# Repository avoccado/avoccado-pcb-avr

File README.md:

Avoccado° PCB layouts and schematics
================

**Most recent version: Avoccado° Felina**

This repository contains the source files of the PCBs for Avoccado° controllers equipped with AVR micro controllers.

There are different PCBs, some with more than one revision. Check the commit log for the most recent development version.

 - Alpha 1 (A1): 8/10 mil width/spacing, 2 sided, components on one side, full size rectangular board a la Arduino Nano / Pro Mini with female micro USB 2.0 and LiPo charger
 - Kane: 8/8 mil, small square board without LiPo charger, components on both sides, good as a tiny RX (receiver) node.
 - Yolandi: 8/8 mil, never tested
 - Nora 1: square board, about one square inch, IRQ from NRF24 routed to MCU
 - Nora 2: same as Nora 1 with IRQ from NRF24 and MPU6050 routed to MCU
 - Faye: updated Nora 2 with voltage divider to sense battery voltage and derive SOC (state of charge), added optional micro USB SMD socket on bottom layer, optionally less part diversity count as R_charge-program can be set with two serialised 1K 0402 resistors. Faye has got an equal 100 mil grid for every pin header and test point.
 - Felina: Features like Faye, without 0402 R_charge-program, non-square footprint, with MPU6050 QFN on board (optional), USB SMD on bottom layer
 - Gin: Board layout smaller than one NRF24L01 PCB module, features AtMega328 QFN + MPU6050 QFN. Not possible to hand solder, very small overall footprint. USB connector only passive (for charging)

Alpha 1 (A1):
----------------

USB bootloader option to update the firmware if the 68R resistors are populated. The USB data lines connect to D2 and D7.
There is a 2K pullup to 3.3V at the D- USB data line, no zener diodes to limit the voltage at the data lines because the MCU runs at USB compliant 3.3V VCC, see vUSB recommendations here: http://vusb.wikidot.com/hardware

Kane
----------------

Smallest version when MPU6050 board not used. Hard to populate due to parts on both sides. Good for tiny receiver nodes, can be hidden in the E27 socket of a light bulb, wall socket..

Nora
----------------

Notes and ideas: No cinsistent 100 mil grid with all headers at the moment
Plated half holes are nice for SMD piggybacking the hole board. Mind the test points and exposed pads on the bottom.

Faye
----------------

Consistent 100 mil grid for all pin headers, additional test points (all conforming the 100 mil grid).
Tighter spacing with 0402 parts now close to the MCU and border of the board.
Battery voltage fed into ADC portpin through high impedance voltage divider to estimate SOC with the MCU.
Optional micro USB socket on the bottom. Data lines not used as of now due to routing constraints, only used for power and charging LiPo batteries.

Felina
----------------

InvenSense MPU6000 / MPU6050 QFN package on board instead of peripheral daughter board. Header for peripheral board still available. Slim rectangular design, slightly longer due to additional parts for onboard MPU, thus only 10 PCBs per panel instead of the usual 16.
Battery voltage fed into ADC portpin through high impedance voltage divider to estimate SOC with the MCU.
Optional: Micro USB female on bottom side for charging
Optional: V-USB components with 2K pullup on D- to enable USB firmware usage. (needs airwire for one data line) 
Attention: V-USB uses same D2 IRQ line as MPU6050.
Consistent 100 mil grid for all pin headers, additional test points, SMD pad for vibration motor output.

Gin
----------------

InvenSense MPU6050 QFN package, Atmel AtMega328p QFN package, very small overall footprint, smaller than a NRF24 module. No seperate ICSP header, flashing only via test points and the NRF24 connector. No DTR reset latch with capacitor.
Consistent 100 mil grid for all headers and test points. 

Panels 
----------------

Boards are either panelized to 50 x 50 mm² or 100 x 100 mm² because my test jig can hold those two sizes. PCBs are usually placed on a 25 mm grid - that is slightly below one inch (25.4 mm).

Test jigs
----------------
Nora 2 test jig is compatible with Nora 1 and Nora 2
See separate repository for test jig assemblies

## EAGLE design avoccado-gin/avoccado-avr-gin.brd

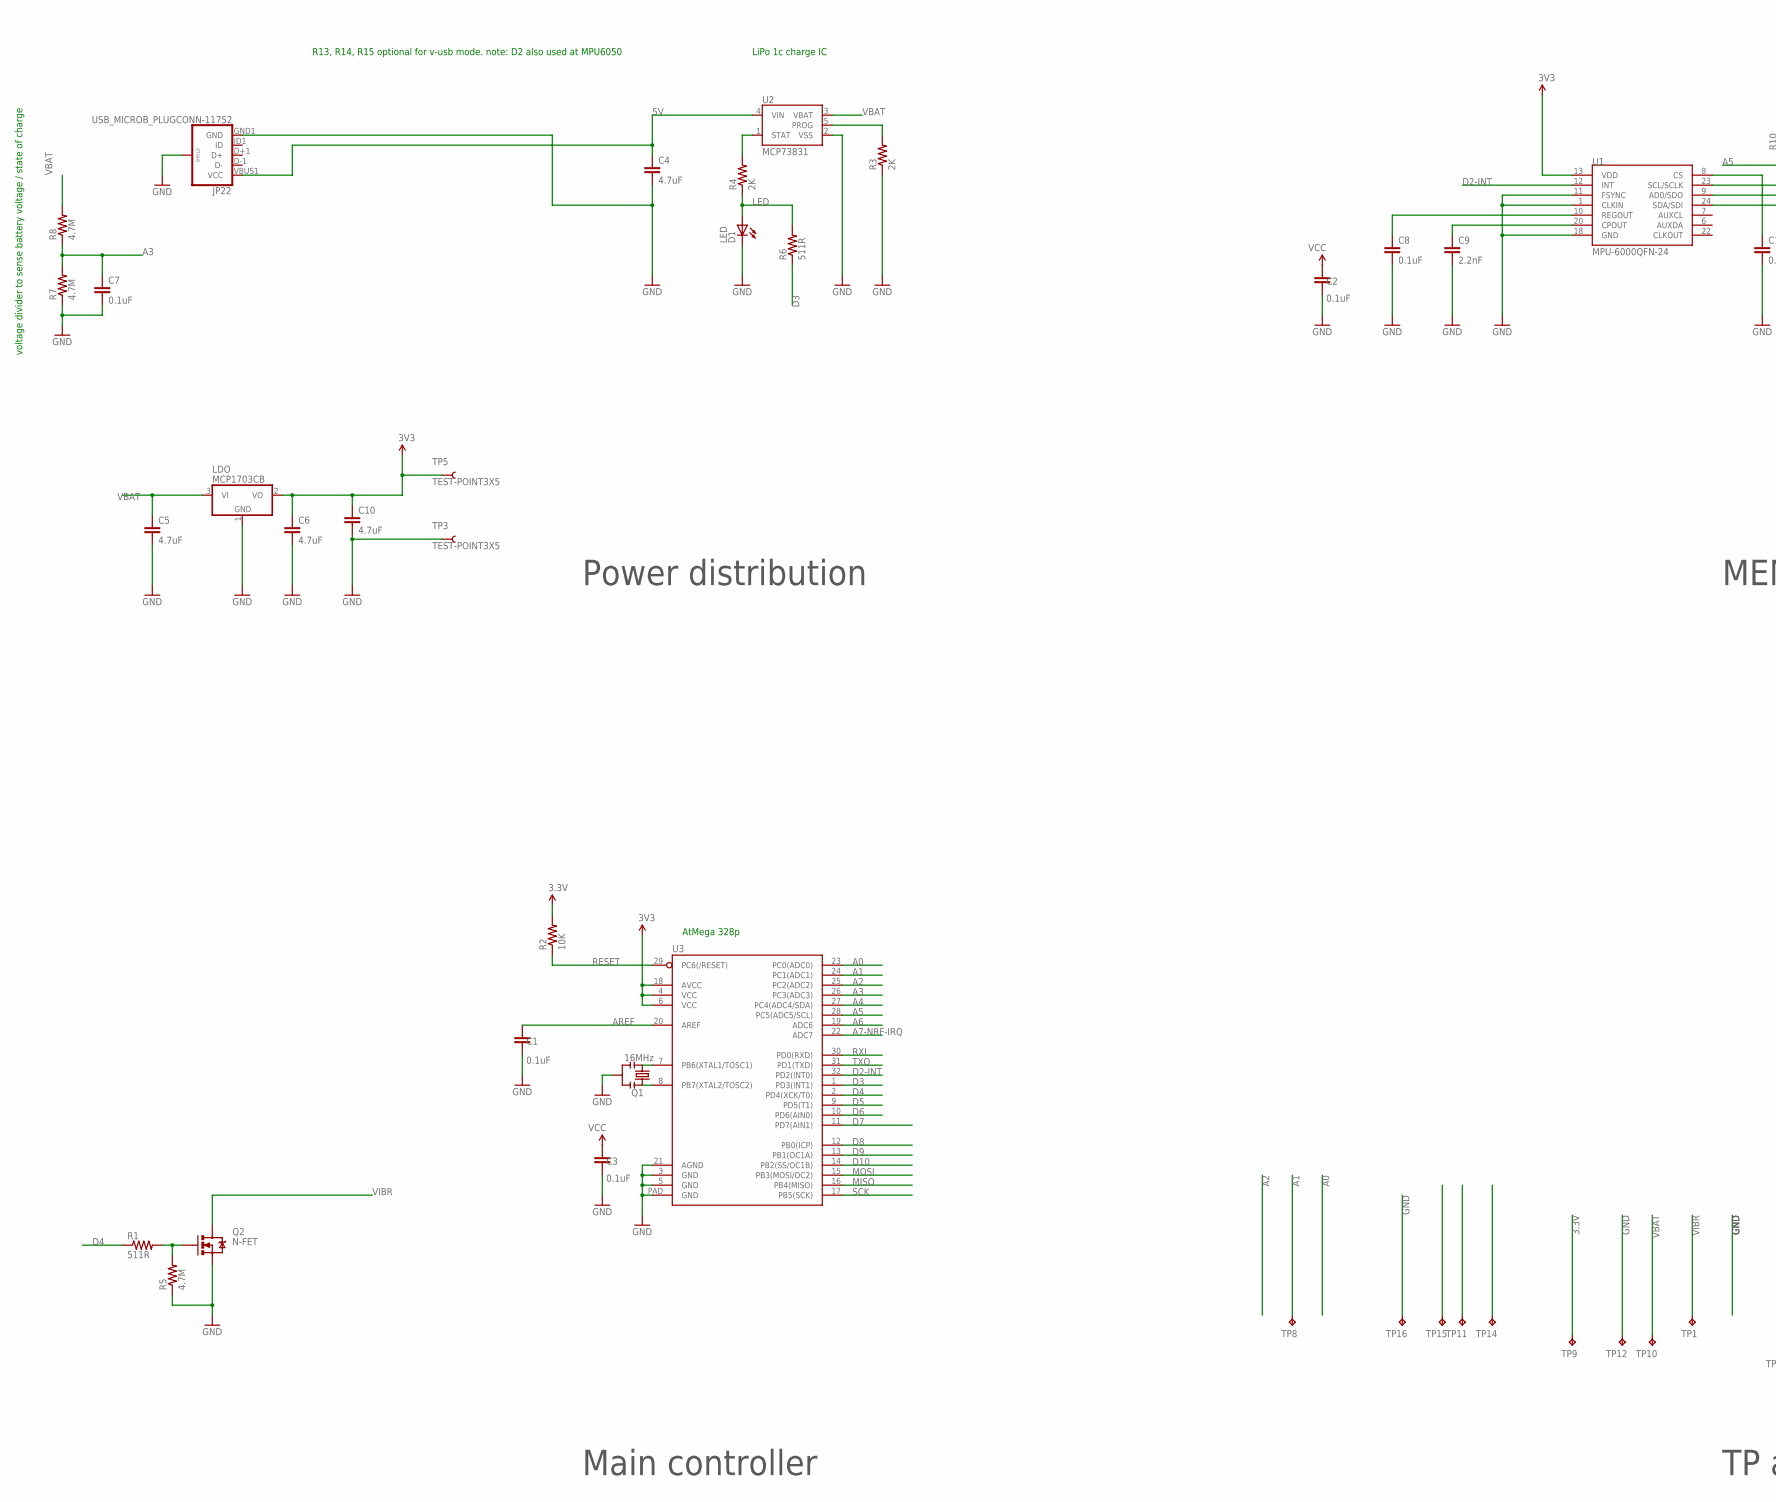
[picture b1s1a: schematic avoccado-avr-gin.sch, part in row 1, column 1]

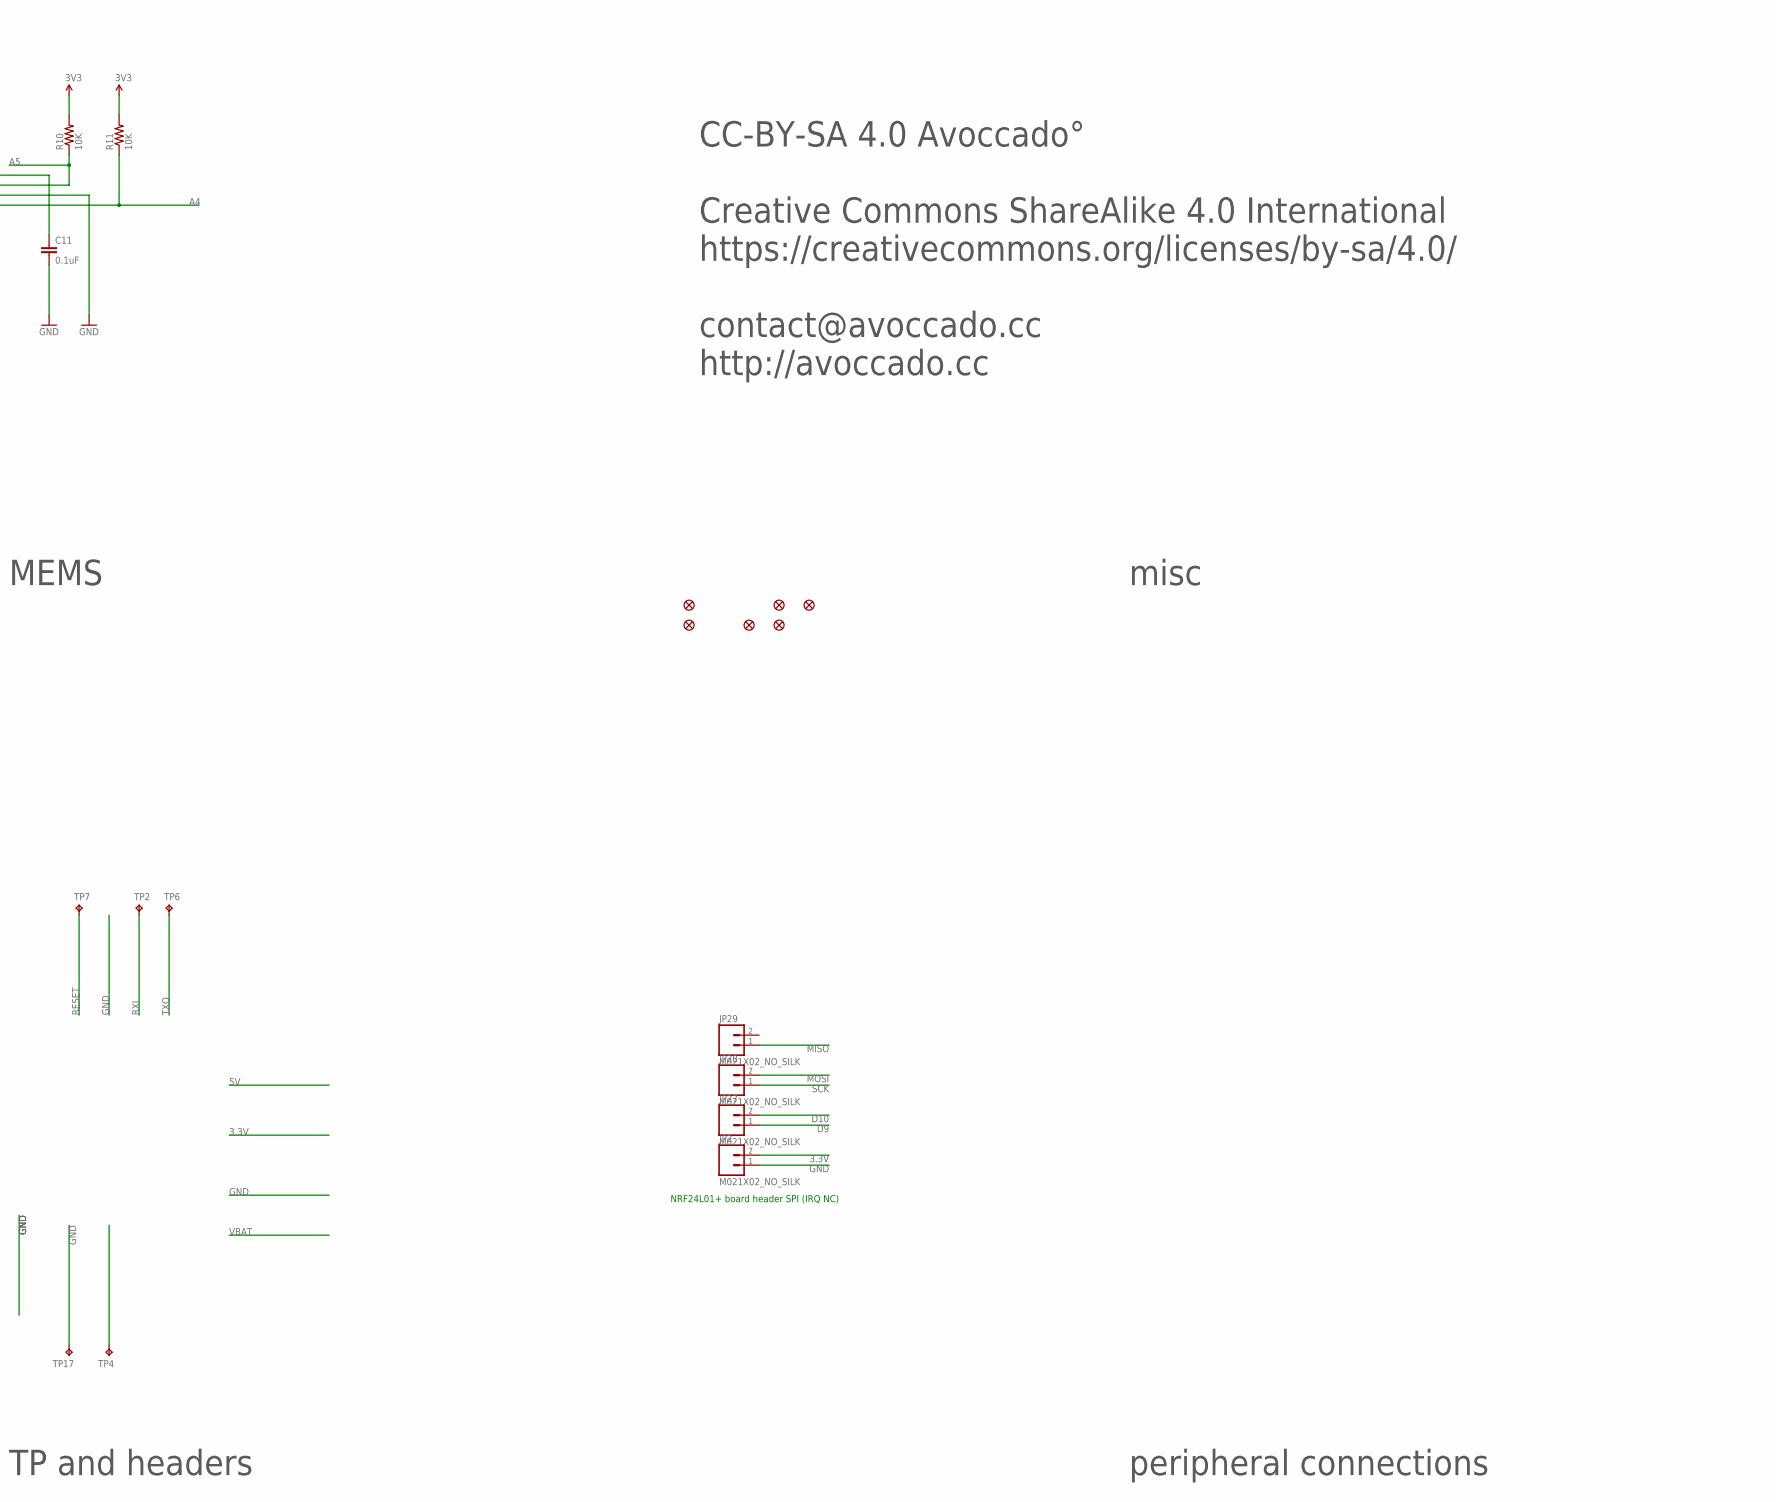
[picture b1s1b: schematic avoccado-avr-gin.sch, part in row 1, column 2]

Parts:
C1, C2, C3, C7, C8, C11: 0.1uF; C0402K
C4, C5, C6: 4.7uF; 0603-CAP
C9: 2.2nF; C0402K
C10: 4.7uF; C0603
D1: LED; LED-0603
FID2, FID4, FID5, FID6, FID8, FID9: FIDUCIALUFIDUCIAL; MICRO-FIDUCIAL
JP2, JP27, JP28, JP29: M021X02_NO_SILK; 1X02_NO_SILK
JP22: USB_MICROB_PLUGCONN-11752; USB-B-MICRO-SMD_V03
LDO: MCP1703CB; SOT23
Q1: 16MHz; RESONATOR-SMD
Q2: N-FET; SOT23-3
R1, R6: 511R; 0603-RES
R2, R10, R11: 10K; 0603-RES
R3, R4: 2K; 0603-RES
R5, R7, R8: 4.7M; 0603-RES
TP1, TP2, TP4, TP6, TP7, TP8, TP9, TP10, TP11, TP12, TP14, TP15, TP16, TP17: TPTP20R; TP20R
TP3, TP5: TEST-POINT3X5; PAD.03X.05
U1: MPU-6000QFN-24; QFN-24-TESTING
U2: MCP73831; SOT23-5
U3: ATMEGA328P_MLFMLF32; MLF32-PAD

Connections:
3.3V: C2.2, C3.2, C6.1, C10.1, JP2.2, LDO.2 (VO), R2.2, R10.2, R11.2, TP5.P$1, TP9.TP, U1.13 (VDD), U3.4 (VCC), U3.6 (VCC), U3.18 (AVCC)
5V: C4.1, JP22.VBUS1 (VCC), U2.4 (VIN)
A0: U3.23 (PC0(ADC0))
A1: TP8.TP, U3.24 (PC1(ADC1))
A2: U3.25 (PC2(ADC2))
A3: C7.1, R7.2, R8.1, U3.26 (PC3(ADC3))
A4: R11.1, U1.24 (SDA/SDI), U3.27 (PC4(ADC4/SDA))
A5: R10.1, U1.23 (SCL/SCLK), U3.28 (PC5(ADC5/SCL))
A6: U3.19 (ADC6)
A7-NRF-IRQ: U3.22 (ADC7)
AREF: C1.2, U3.20 (AREF)
CHG-PROG: R3.2, U2.5 (PROG)
D2-INT: U1.12 (INT), U3.32 (PD2(INT0))
D3: R6.1, U3.1 (PD3(INT1))
D4: R1.1, U3.2 (PD4(XCK/T0))
D5: TP15.TP, U3.9 (PD5(T1))
D6: U3.10 (PD6(AIN0))
D7: TP14.TP, U3.11 (PD7(AIN1))
D8: TP11.TP, U3.12 (PB0(ICP))
D9: JP27.1, U3.13 (PB1(OC1A))
D10: JP27.2, U3.14 (PB2(SS/OC1B))
GND: C1.1, C2.1, C3.1, C4.2, C5.2, C6.2, C7.2, C8.2, C9.2, C10.2, C11.2, D1.C, JP2.1, JP22.GND1 (GND), JP22.SHIELD1 (SHIELD), JP22.SHIELD2 (SHIELD), JP22.SHIELD3 (SHIELD), LDO.1 (GND), Q1.2, Q2.2 (S), R3.1, R5.1, R7.1, TP3.P$1, TP12.TP, TP16.TP, TP17.TP, U1.1 (CLKIN), U1.9 (AD0/SDO), U1.11 (FSYNC), U1.18 (GND), U2.2 (VSS), U3.3 (GND), U3.5 (GND), U3.21 (AGND), U3.PAD (GND)
LED: D1.A, R4.1, R6.2
MISO: JP29.1, U3.16 (PB4(MISO))
MOSI: JP28.2, U3.15 (PB3(MOSI/OC2))
unnamed: Q1.1, U3.8 (PB7(XTAL2/TOSC2))
unnamed: Q1.3, U3.7 (PB6(XTAL1/TOSC1))
unnamed: Q2.1 (G), R1.2, R5.2
unnamed: C8.1, U1.10 (REGOUT)
unnamed: C9.1, U1.20 (CPOUT)
unnamed: C11.1, U1.8 (CS)
RESET: R2.1, TP7.TP, U3.29 (PC6(/RESET))
RXI: TP2.TP, U3.30 (PD0(RXD))
SCK: JP28.1, U3.17 (PB5(SCK))
SOC: R4.2, U2.1 (STAT)
TXO: TP6.TP, U3.31 (PD1(TXD))
VBAT: C5.1, LDO.3 (VI), R8.2, TP4.TP, TP10.TP, U2.3 (VBAT)
VIBR: Q2.3 (D), TP1.TP

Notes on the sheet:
NRF24L01+ board header SPI (IRQ NC)
AtMega 328p
LiPo 1c charge IC
voltage divider to sense battery voltage / state of charge
R13, R14, R15 optional for v-usb mode. note: D2 also used at MPU6050
Power distribution
Main controller
TP and headers
peripheral connections
misc
MEMS
CC-BY-SA 4.0 Avoccado° Creative Commons ShareAlike 4.0 International https://creativecommons.org/licenses/by-sa/4.0/ contact@avoccado.cc http://avoccado.cc

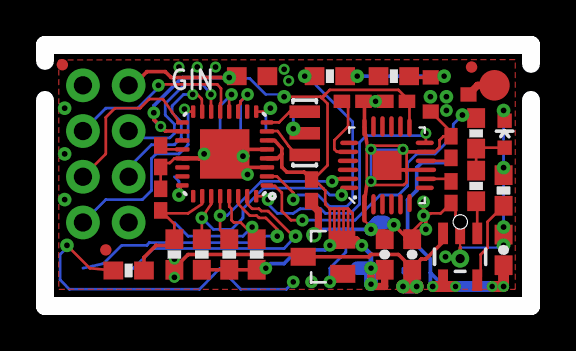
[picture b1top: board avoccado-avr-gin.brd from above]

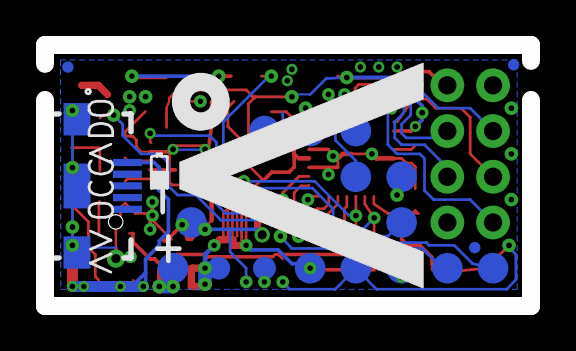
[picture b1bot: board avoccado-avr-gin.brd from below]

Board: 2 copper layers, 27.0 x 14.5 mm, 55 parts (19 on the bottom side), 33 nets.

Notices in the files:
avoccado-avr-pcb.sch:
Released under the Creative Commons Attribution Share-Alike 4.0 License
parts and their libraries:
SparkFun-DiscreteSemi: Licensing: Creative Commons ShareAlike 4.0 International - https://creativecommons.org/licenses/by-sa/4.0
